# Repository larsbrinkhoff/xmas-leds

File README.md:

- ATmega328P on a breadboard
- SK6812 strip
- Forth cross compiler

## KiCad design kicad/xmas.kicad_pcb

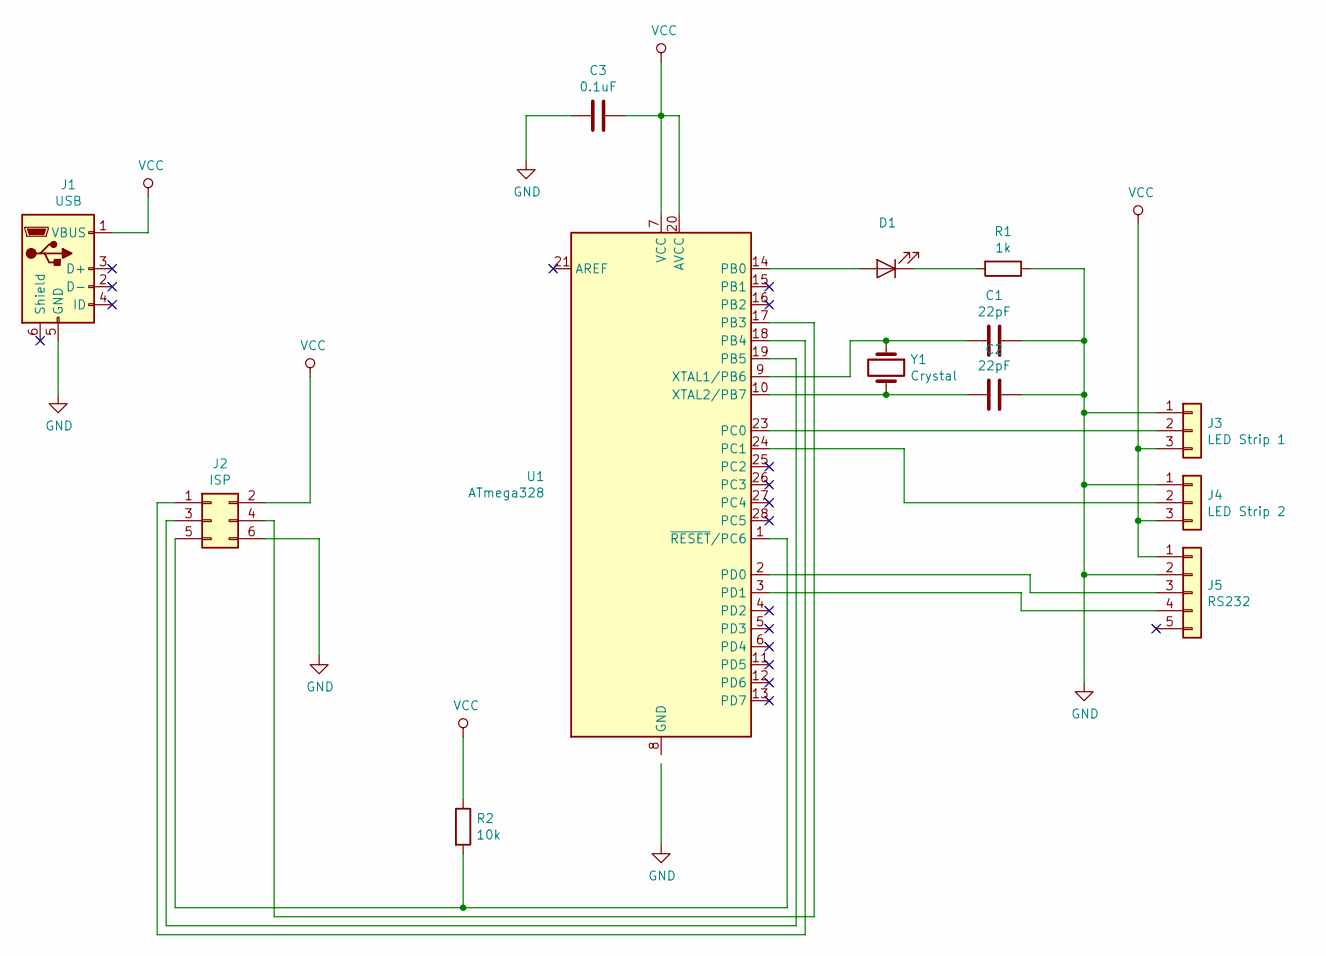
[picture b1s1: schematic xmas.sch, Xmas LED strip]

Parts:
C1, C2: 22pF; C_Disc_D7.5mm_W2.5mm_P5.00mm
C3: 0.1uF; C_Disc_D16.0mm_W5.0mm_P7.50mm
D1: LED_D5.0mm
J1: USB; USB_Micro-B_Wuerth_614105150721_Vertical
J2: ISP; IDC-Header_2x03_P2.54mm_Vertical
J3: LED Strip 1; PinHeader_1x03_P2.54mm_Vertical
J4: LED Strip 2; PinHeader_1x03_P2.54mm_Vertical
J5: RS232; PinHeader_1x05_P2.54mm_Vertical
R1: 1k; R_Axial_DIN0207_L6.3mm_D2.5mm_P10.16mm_Horizontal
R2: 10k; R_Axial_DIN0207_L6.3mm_D2.5mm_P10.16mm_Horizontal
U1: ATmega328; DIP-28_W7.62mm_Socket
Y1: Crystal; Crystal_HC49-U_Vertical

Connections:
GND: C1.1, C2.1, C3.2, J1.5 (GND), J2.6, J3.1, J4.1, J5.2, R1.1
unnamed: C1.2, U1.9 (XTAL1/PB6), Y1.1
unnamed: C2.2, U1.10 (XTAL2/PB7), Y1.2
unnamed: D1.1 (K), R1.2
unnamed: D1.2 (A), U1.14 (PB0)
unnamed: J2.1, U1.18 (PB4)
unnamed: J2.3, U1.19 (PB5)
unnamed: J2.4, U1.17 (PB3)
unnamed: J2.5, R2.2, U1.1 (~RESET~/PC6)
unnamed: J3.2, U1.23 (PC0)
unnamed: J4.2, U1.24 (PC1)
unnamed: J5.3, U1.2 (PD0)
unnamed: J5.4, U1.3 (PD1)
unnamed: U1.8 (GND), U1.22 (GND)
VCC: C3.1, J1.1 (VBUS), J2.2, J3.3, J4.3, J5.1, R2.1, U1.7 (VCC), U1.20 (AVCC)

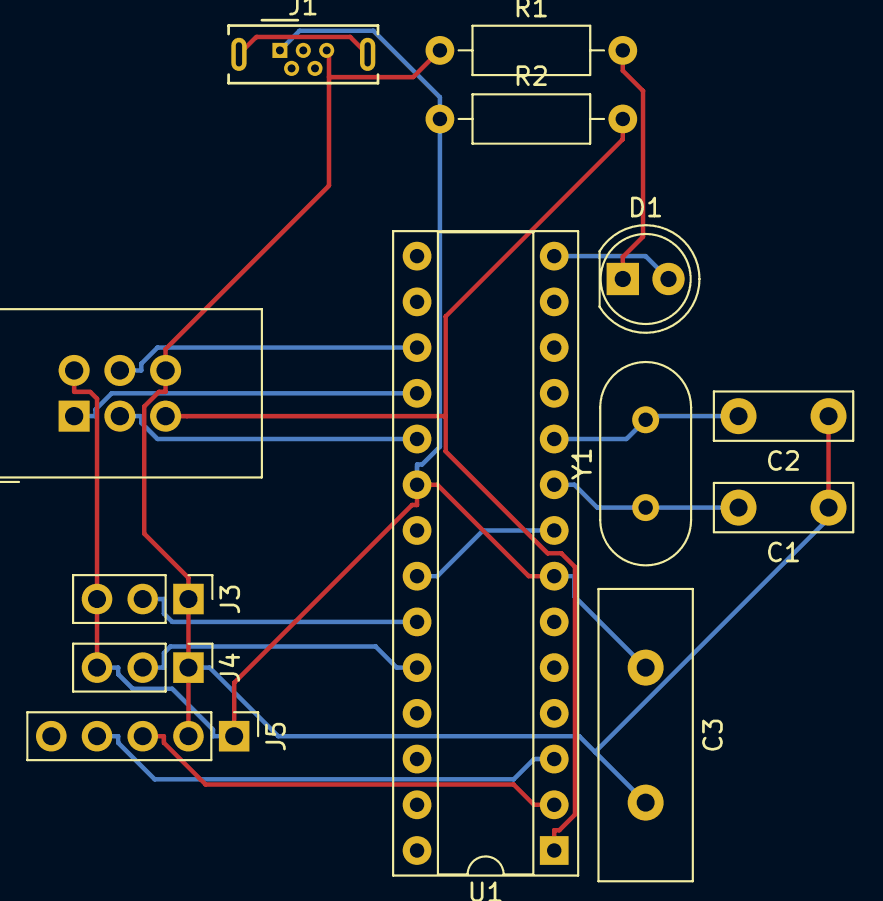
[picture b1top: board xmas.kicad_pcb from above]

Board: 2 copper layers, 13 parts (0 on the bottom side), 15 nets.

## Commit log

2019-12-11 Description.
2019-12-11 Forth code.
2019-12-11 Convenience for building and uploading.
2020-01-11 Photo.
2020-01-11 Update code.
2020-12-17 Move avrdude command to makefile variable.
2020-12-17 Program fuses for 16 MHz external oscillator.
2020-12-21 KiCad project.
